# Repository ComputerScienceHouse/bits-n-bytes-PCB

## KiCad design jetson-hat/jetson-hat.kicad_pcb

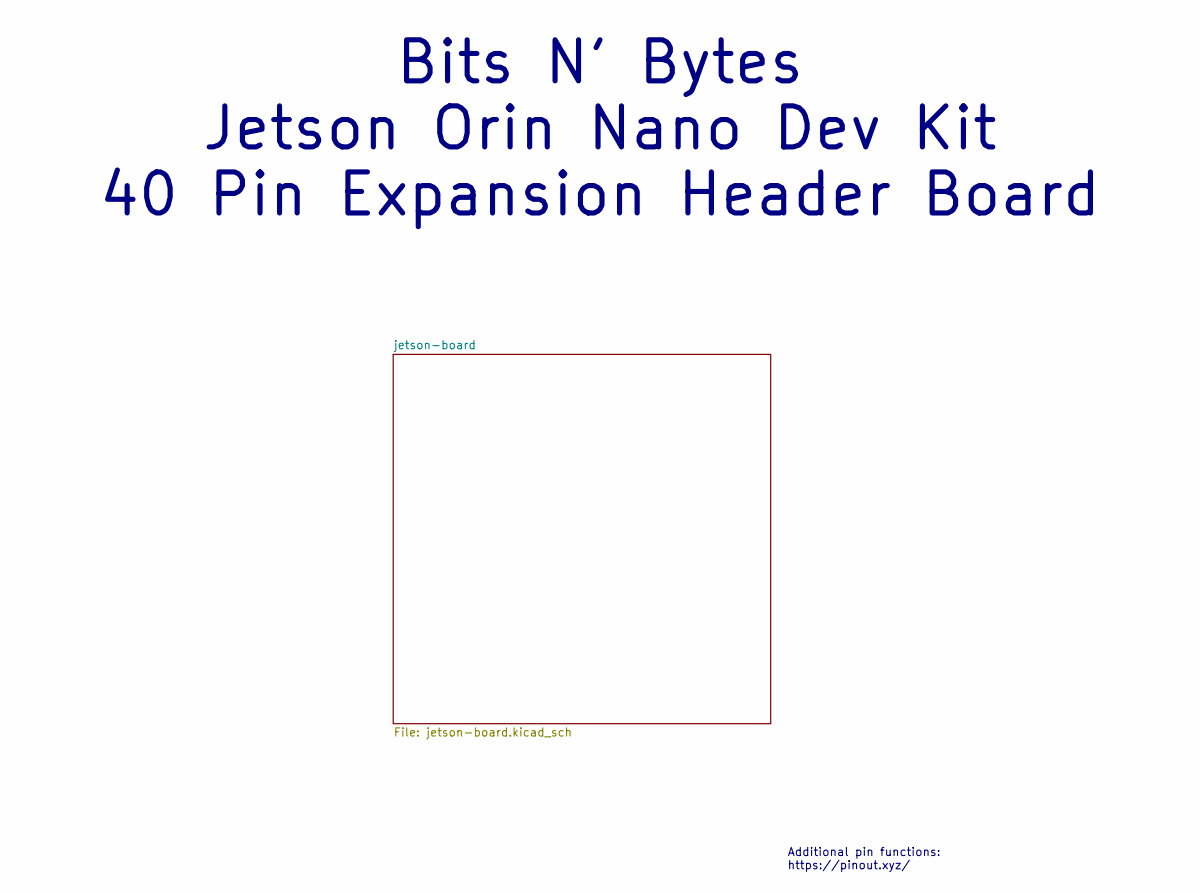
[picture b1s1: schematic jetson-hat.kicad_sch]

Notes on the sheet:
Additional pin functions: https://pinout.xyz/
Bits N' Bytes Jetson Orin Nano Dev Kit 40 Pin Expansion Header Board

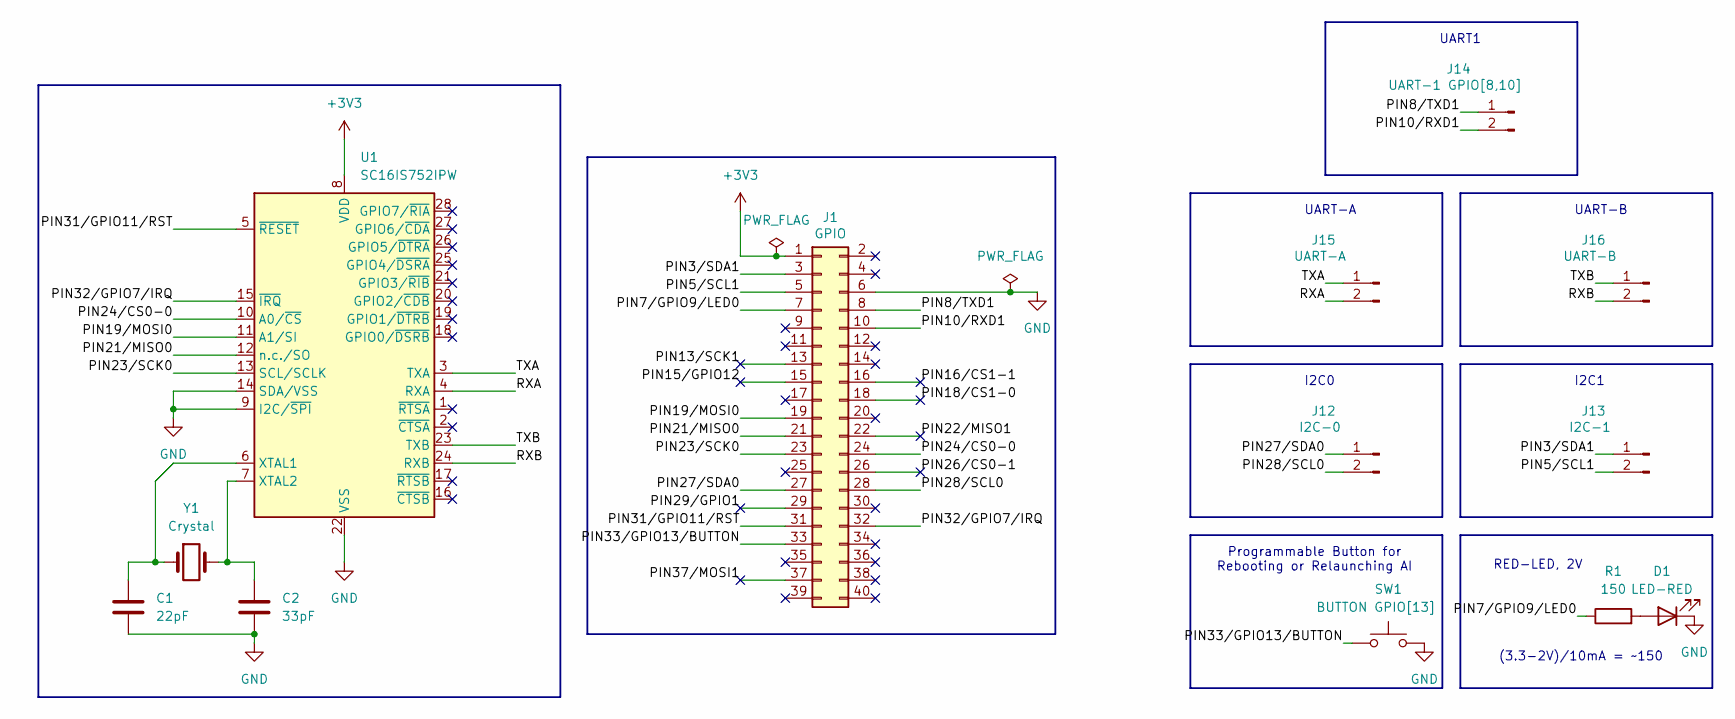
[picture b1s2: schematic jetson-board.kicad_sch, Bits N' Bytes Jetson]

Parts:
C1: 22pF; C_1206_3216Metric_Pad1.33x1.80mm_HandSolder
C2: 33pF; C_1206_3216Metric_Pad1.33x1.80mm_HandSolder
D1: LED-RED; LED_0805_2012Metric_Pad1.15x1.40mm_HandSolder
J1: GPIO; PinSocket_2x20_P2.54mm_Vertical
J12: I2C-0; Molex_Mini-Fit_Jr_5566-02A_2x01_P4.20mm_Vertical
J13: I2C-1; Molex_Mini-Fit_Jr_5566-02A_2x01_P4.20mm_Vertical
J14: UART-1 GPIO[8,10]; Molex_Mini-Fit_Jr_5566-02A_2x01_P4.20mm_Vertical
J15: UART-A; Molex_Mini-Fit_Jr_5566-02A_2x01_P4.20mm_Vertical
J16: UART-B; Molex_Mini-Fit_Jr_5566-02A_2x01_P4.20mm_Vertical
R1: 150; R_1206_3216Metric_Pad1.30x1.75mm_HandSolder
SW1: BUTTON GPIO[13]; SW_NKK_GW12LJP
U1: SC16IS752IPW; TSSOP-28_4.4x9.7mm_P0.65mm
Y1: Crystal; Crystal_SMD_5032-2Pin_5.0x3.2mm_HandSoldering

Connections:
+3V3: J1.1, U1.8 (VDD)
/jetson-board/PIN3/SDA1: J1.3, J13.1
/jetson-board/PIN5/SCL1: J1.5, J13.2
/jetson-board/PIN7/GPIO9/LED0: J1.7, R1.1
/jetson-board/PIN8/TXD1: J1.8, J14.1
/jetson-board/PIN10/RXD1: J1.10, J14.2
/jetson-board/PIN13/SCK1: J1.13
/jetson-board/PIN15/GPIO12: J1.15
/jetson-board/PIN16/CS1-1: J1.16
/jetson-board/PIN18/CS1-0: J1.18
/jetson-board/PIN19/MOSI0: J1.19, U1.11 (A1/SI)
/jetson-board/PIN21/MISO0: J1.21, U1.12 (n.c./SO)
/jetson-board/PIN22/MISO1: J1.22
/jetson-board/PIN23/SCK0: J1.23, U1.13 (SCL/SCLK)
/jetson-board/PIN24/CS0-0: J1.24, U1.10 (A0/~CS)
/jetson-board/PIN26/CS0-1: J1.26
/jetson-board/PIN27/SDA0: J1.27, J12.1
/jetson-board/PIN28/SCL0: J1.28, J12.2
/jetson-board/PIN29/GPIO1: J1.29
/jetson-board/PIN31/GPIO11/RST: J1.31, U1.5 (~RESET)
/jetson-board/PIN32/GPIO7/IRQ: J1.32, U1.15 (~IRQ)
/jetson-board/PIN33/GPIO13/BUTTON: J1.33, SW1.1
/jetson-board/PIN37/MOSI1: J1.37
/jetson-board/RXA: J15.2, U1.4 (RXA)
/jetson-board/RXB: J16.2, U1.24 (RXB)
/jetson-board/TXA: J15.1, U1.3 (TXA)
/jetson-board/TXB: J16.1, U1.23 (TXB)
GND: C1.2, C2.2, D1.1 (K), J1.6, SW1.2, U1.9 (I2C/~SPI), U1.14 (SDA/VSS), U1.22 (VSS)
unnamed: D1.2 (A), R1.2
unnamed: C1.1, U1.6 (XTAL1), Y1.1
unnamed: C2.1, U1.7 (XTAL2), Y1.2

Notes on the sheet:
I2C1
UART-A
Programmable Button for Rebooting or Relaunching AI
UART1
I2C0
RED-LED, 2V
UART-B
(3.3-2V)/10mA = ~150

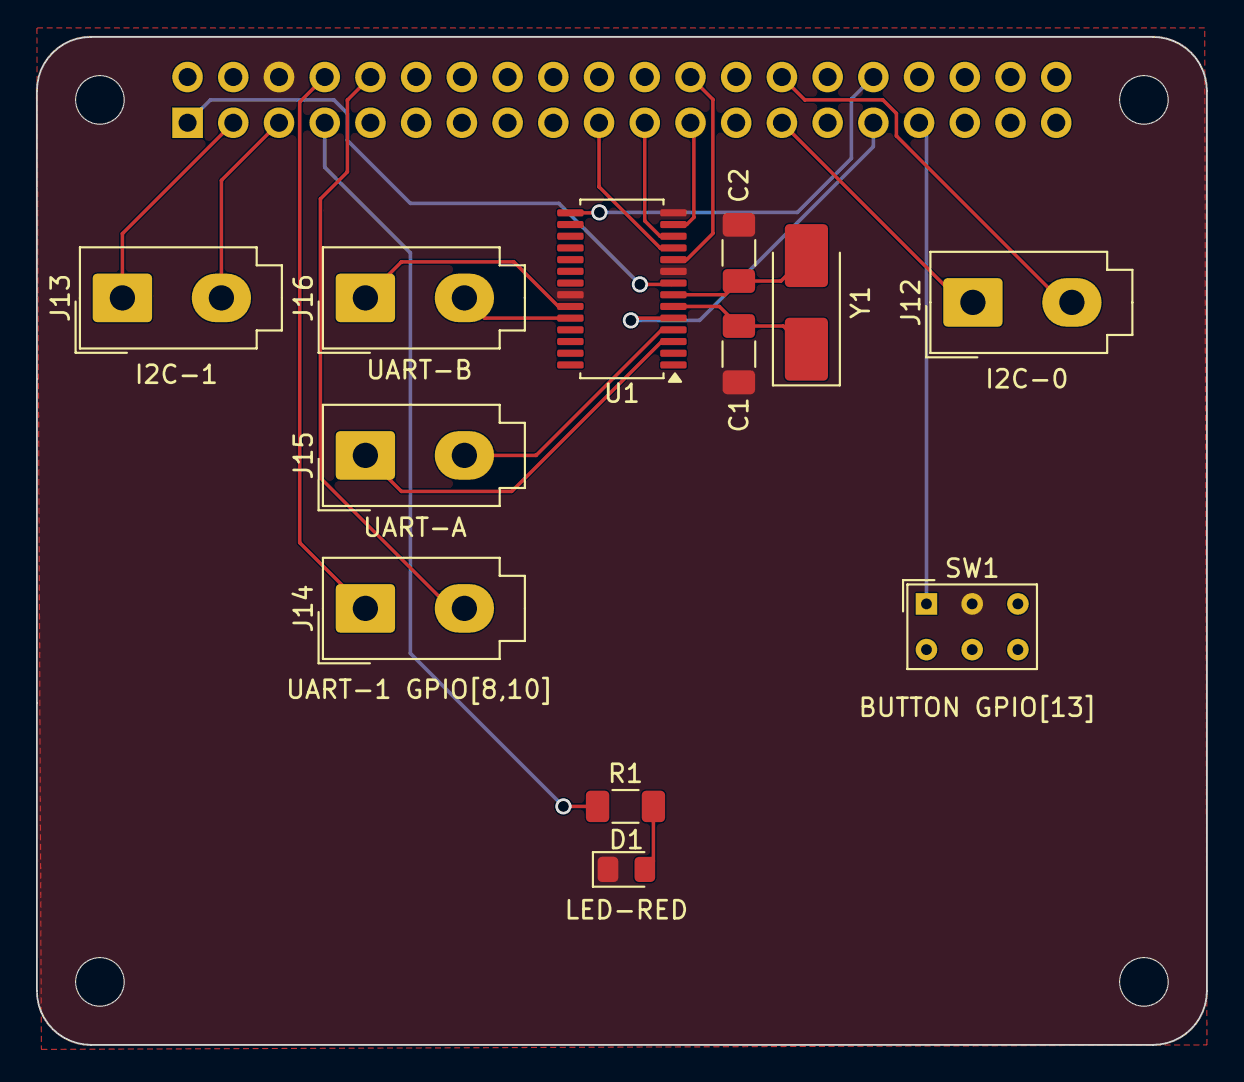
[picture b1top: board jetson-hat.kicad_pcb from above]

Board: 2 copper layers, 65.0 x 56.0 mm, 17 parts (1 on the bottom side), 23 nets.

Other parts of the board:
MH1, MH2, MH3, MH4: MountingHole_2.7mm_M2.5

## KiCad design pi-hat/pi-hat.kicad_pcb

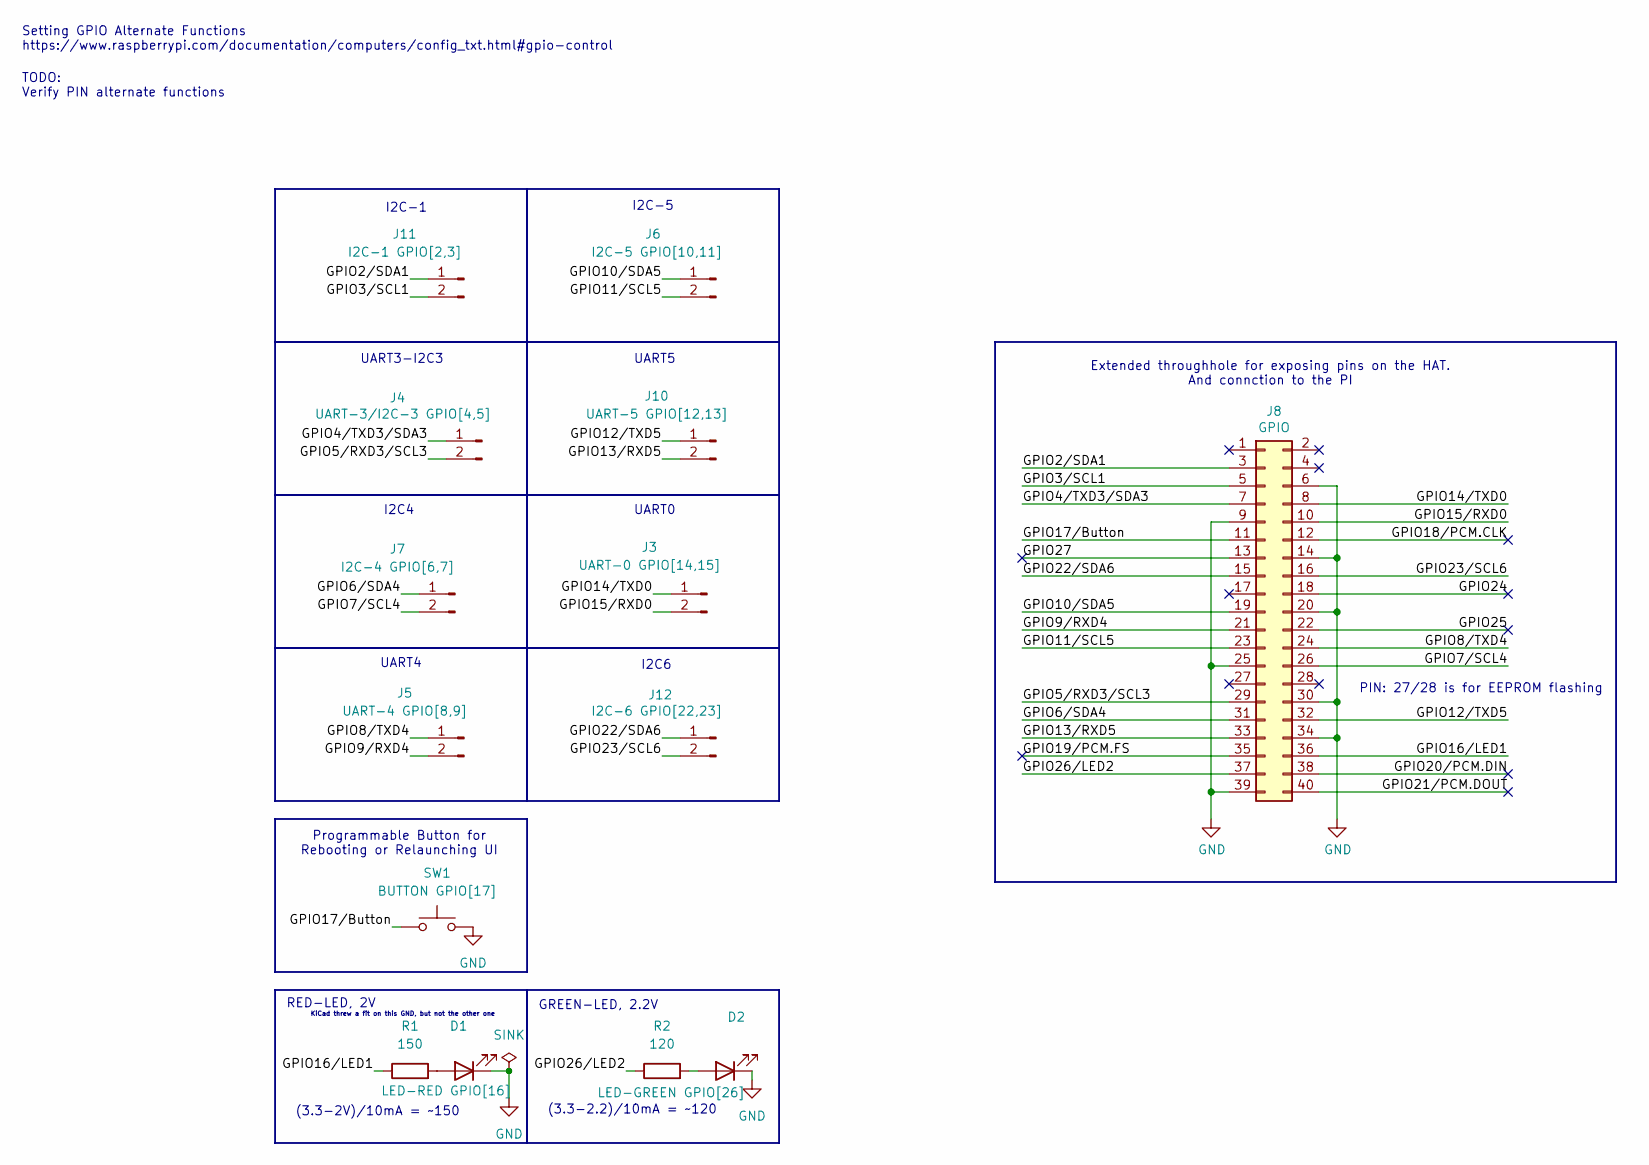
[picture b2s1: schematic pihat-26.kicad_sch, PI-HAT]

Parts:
D1: LED-RED GPIO[16]; LED_0805_2012Metric_Pad1.15x1.40mm_HandSolder
D2: LED-GREEN GPIO[26]; LED_0805_2012Metric_Pad1.15x1.40mm_HandSolder
J3: UART-0 GPIO[14,15]; Molex_Mini-Fit_Jr_5566-02A_2x01_P4.20mm_Vertical
J4: UART-3/I2C-3 GPIO[4,5]; Molex_Mini-Fit_Jr_5566-02A_2x01_P4.20mm_Vertical
J5: UART-4 GPIO[8,9]; Molex_Mini-Fit_Jr_5566-02A_2x01_P4.20mm_Vertical
J6: I2C-5 GPIO[10,11]; Molex_Mini-Fit_Jr_5566-02A_2x01_P4.20mm_Vertical
J7: I2C-4 GPIO[6,7]; Molex_Mini-Fit_Jr_5566-02A_2x01_P4.20mm_Vertical
J8: GPIO; PinSocket_2x20_P2.54mm_Vertical
J10: UART-5 GPIO[12,13]; Molex_Mini-Fit_Jr_5566-02A_2x01_P4.20mm_Vertical
J11: I2C-1 GPIO[2,3]; Molex_Mini-Fit_Jr_5566-02A_2x01_P4.20mm_Vertical
J12: I2C-6 GPIO[22,23]; Molex_Mini-Fit_Jr_5566-02A_2x01_P4.20mm_Vertical
R1: 150; R_1206_3216Metric_Pad1.30x1.75mm_HandSolder
R2: 120; R_1206_3216Metric_Pad1.30x1.75mm_HandSolder
SW1: BUTTON GPIO[17]; SW_NKK_GW12LJP

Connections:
/PI-HAT/GPIO2/SDA1: J8.3, J11.1
/PI-HAT/GPIO3/SCL1: J8.5, J11.2
/PI-HAT/GPIO4/TXD3/SDA3: J4.1, J8.7
/PI-HAT/GPIO5/RXD3/SCL3: J4.2, J8.29
/PI-HAT/GPIO6/SDA4: J7.1, J8.31
/PI-HAT/GPIO7/SCL4: J7.2, J8.26
/PI-HAT/GPIO8/TXD4: J5.1, J8.24
/PI-HAT/GPIO9/RXD4: J5.2, J8.21
/PI-HAT/GPIO10/SDA5: J6.1, J8.19
/PI-HAT/GPIO11/SCL5: J6.2, J8.23
/PI-HAT/GPIO12/TXD5: J8.32, J10.1
/PI-HAT/GPIO13/RXD5: J8.33, J10.2
/PI-HAT/GPIO14/TXD0: J3.1, J8.8
/PI-HAT/GPIO15/RXD0: J3.2, J8.10
/PI-HAT/GPIO16/LED1: J8.36, R1.1
/PI-HAT/GPIO17/Button: J8.11, SW1.1
/PI-HAT/GPIO18/PCM.CLK: J8.12
/PI-HAT/GPIO19/PCM.FS: J8.35
/PI-HAT/GPIO20/PCM.DIN: J8.38
/PI-HAT/GPIO21/PCM.DOUT: J8.40
/PI-HAT/GPIO22/SDA6: J8.15, J12.1
/PI-HAT/GPIO23/SCL6: J8.16, J12.2
/PI-HAT/GPIO24: J8.18
/PI-HAT/GPIO25: J8.22
/PI-HAT/GPIO26/LED2: J8.37, R2.1
/PI-HAT/GPIO27: J8.13
GND: D1.1 (K), D2.1 (K), J8.6, J8.9, J8.14, J8.20, J8.25, J8.30, J8.34, J8.39, SW1.2
unnamed: D1.2 (A), R1.2
unnamed: D2.2 (A), R2.2

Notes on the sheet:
I2C4
TODO: Verify PIN alternate functions
KiCad threw a fit on this GND, but not the other one
(3.3-2.2)/10mA = ~120
UART4
UART3-I2C3
PIN: 27/28 is for EEPROM flashing
I2C6
GREEN-LED, 2.2V
RED-LED, 2V
Programmable Button for Rebooting or Relaunching UI
I2C-5
(3.3-2V)/10mA = ~150
UART0
I2C-1
Extended throughhole for exposing pins on the HAT. And connction to the PI
Setting GPIO Alternate Functions https://www.raspberrypi.com/documentation/computers/config_txt.html#gpio-control
UART5

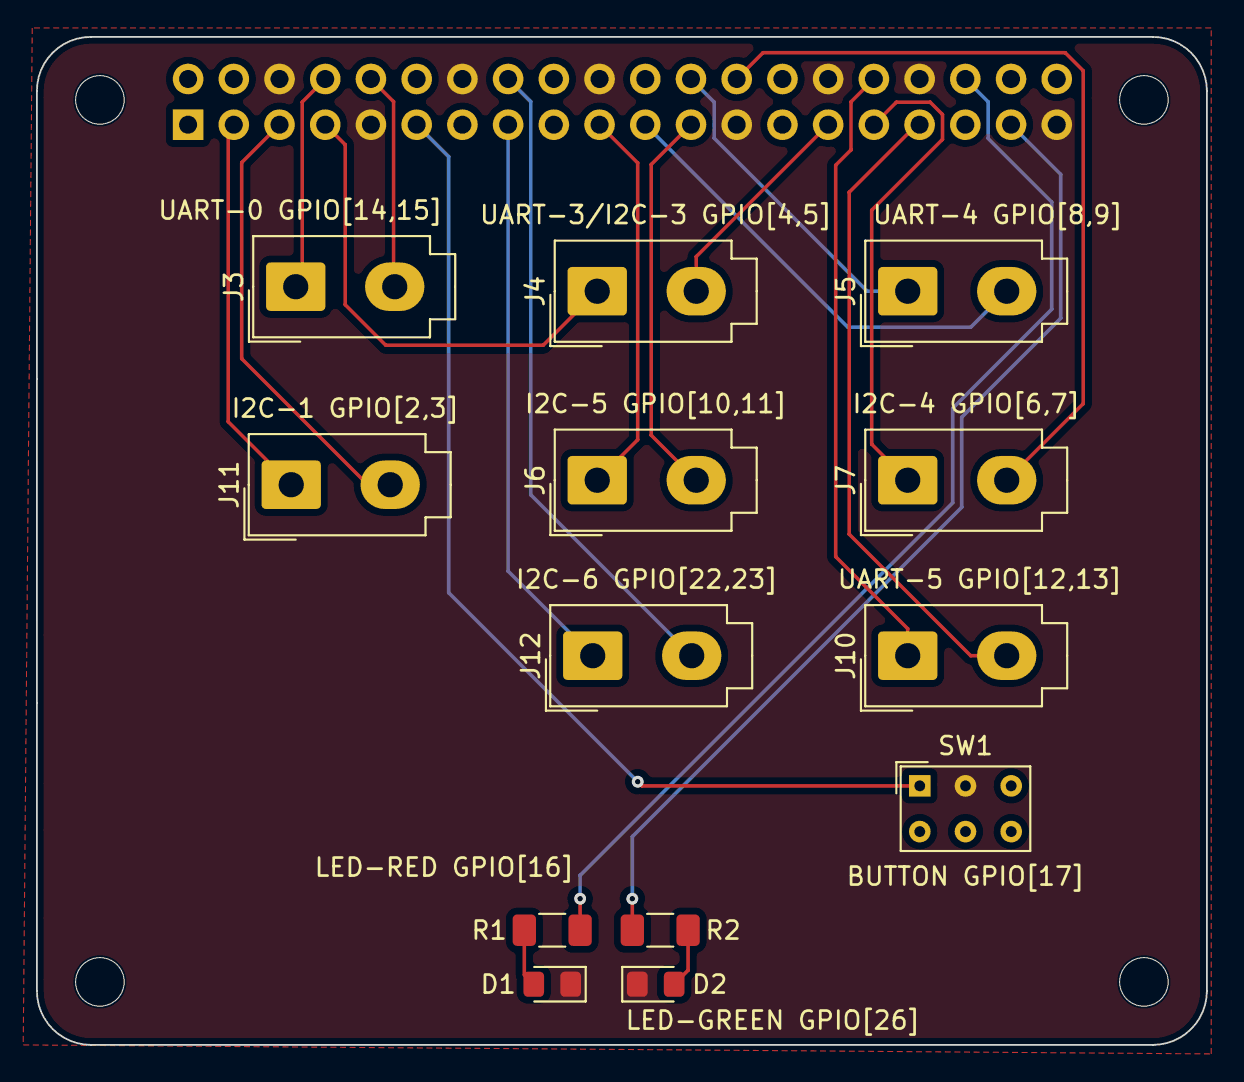
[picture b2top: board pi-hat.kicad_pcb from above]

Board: 2 copper layers, 65.0 x 56.0 mm, 18 parts (1 on the bottom side), 22 nets.

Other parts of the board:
MH1, MH2, MH3, MH4: MountingHole_2.7mm_M2.5
